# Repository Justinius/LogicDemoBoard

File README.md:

# LogicDemoBoard
PCB for simple logic demo

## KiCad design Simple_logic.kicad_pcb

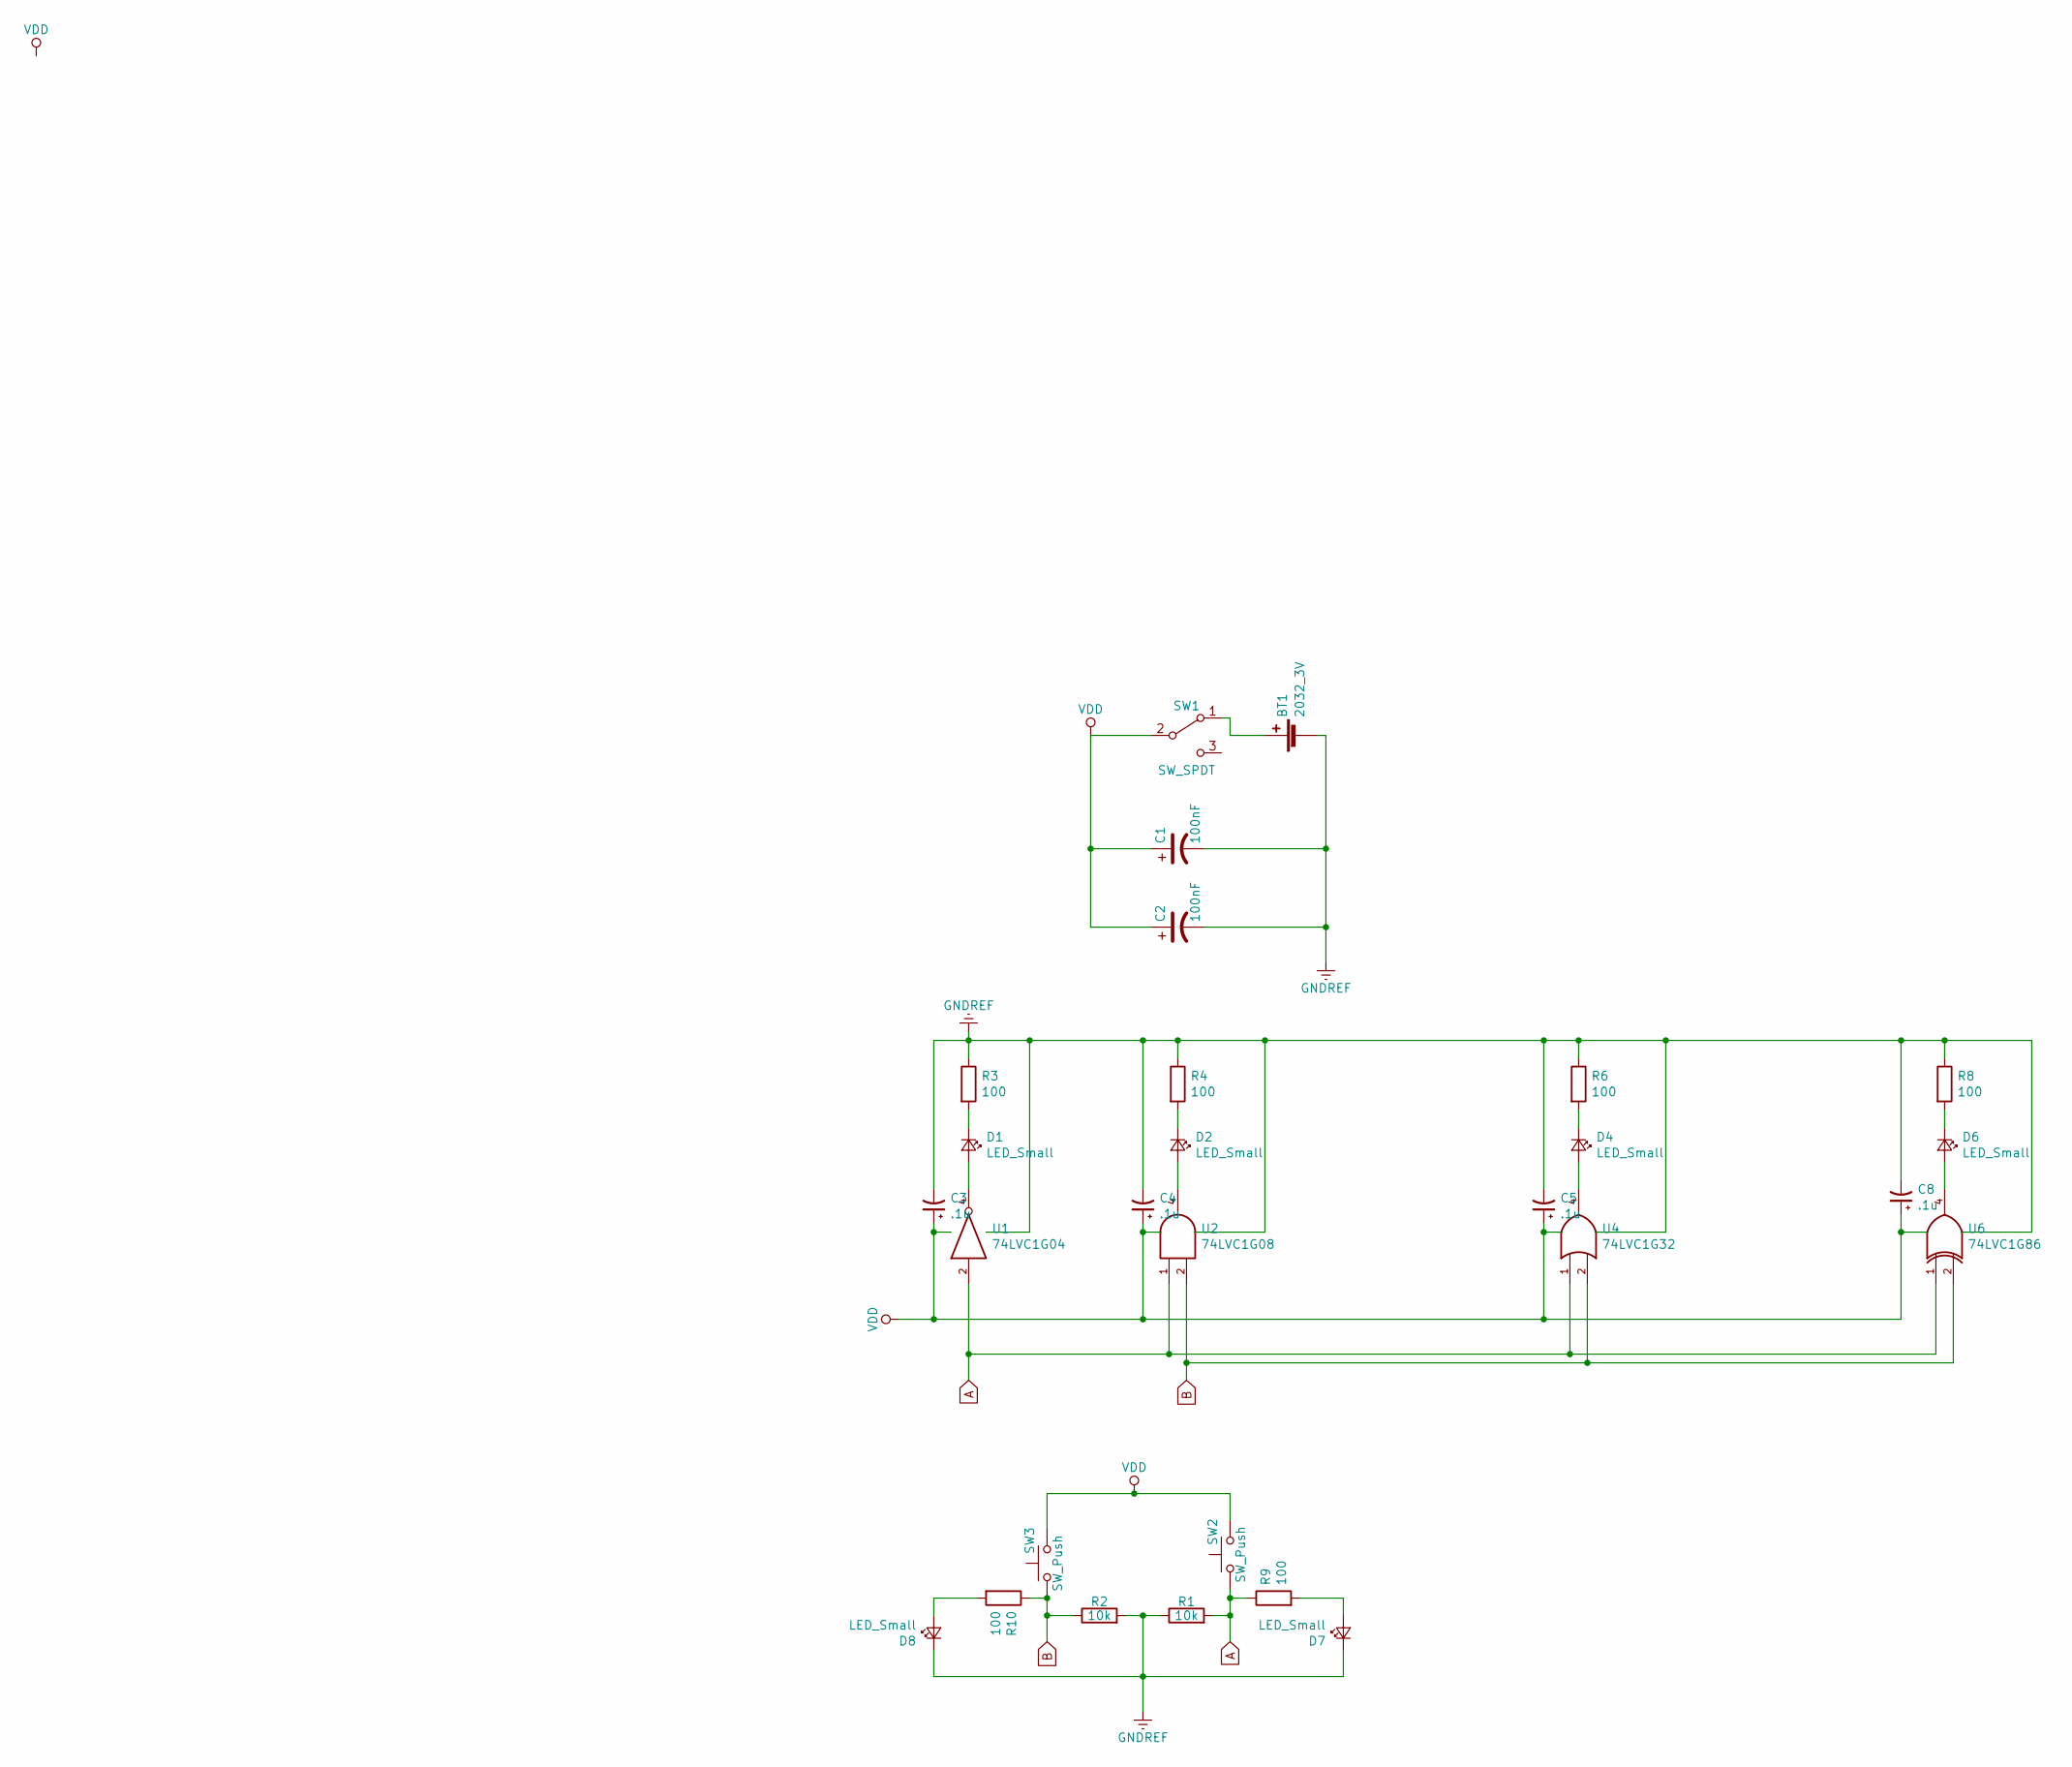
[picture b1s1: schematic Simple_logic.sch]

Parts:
BT1: 2032_3V; Keystone_3034_1x20mm-CoinCell
C1, C2: 100nF; C_0603_HandSoldering
C3, C4, C5, C8: .1u; C_0603_HandSoldering
D1, D2, D4, D6, D7, D8: LED_Small; LED_0805_HandSoldering
R1, R2: 10k; R_0603_HandSoldering
R3, R4, R6, R8, R9, R10: 100; R_0603_HandSoldering
SW1: SW_SPDT; SW_SPDT_CK-JS102011SAQN
SW2, SW3: SW_Push; SW_SPST_PTS645
U1: 74LVC1G04; SOT-23-5_HandSoldering
U2: 74LVC1G08; SOT-23-5_HandSoldering
U4: 74LVC1G32; SOT-23-5_HandSoldering
U6: 74LVC1G86; SOT-23-5_HandSoldering

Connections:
A: R1.2, R9.1, SW2.1, U1.2, U2.1, U4.1, U6.1
B: R2.1, R10.1, SW3.1, U2.2, U4.2, U6.2
GND: BT1.2 (-), C1.2, C2.2, C3.2, C4.2, C5.2, C8.2, D7.1 (K), D8.1 (K), R1.1, R2.2, R3.1, R4.1, R6.1, R8.1, U1.3 (GND), U2.3 (GND), U4.3 (GND), U6.3 (GND); also elsewhere on the board
unnamed: BT1.1 (+), SW1.1 (A)
unnamed: D1.1 (K), R3.2
unnamed: D1.2 (A), U1.4
unnamed: D2.1 (K), R4.2
unnamed: D2.2 (A), U2.4
unnamed: D4.1 (K), R6.2
unnamed: D4.2 (A), U4.4
unnamed: D6.1 (K), R8.2
unnamed: D6.2 (A), U6.4
unnamed: D7.2 (A), R9.2
unnamed: D8.2 (A), R10.2
VCC: C1.1, C2.1, C3.1, C4.1, C5.1, C8.1, SW1.2 (B), SW2.2, SW3.2, U1.5 (VCC), U2.5 (VCC), U4.5 (VCC), U6.5 (VCC); also elsewhere on the board

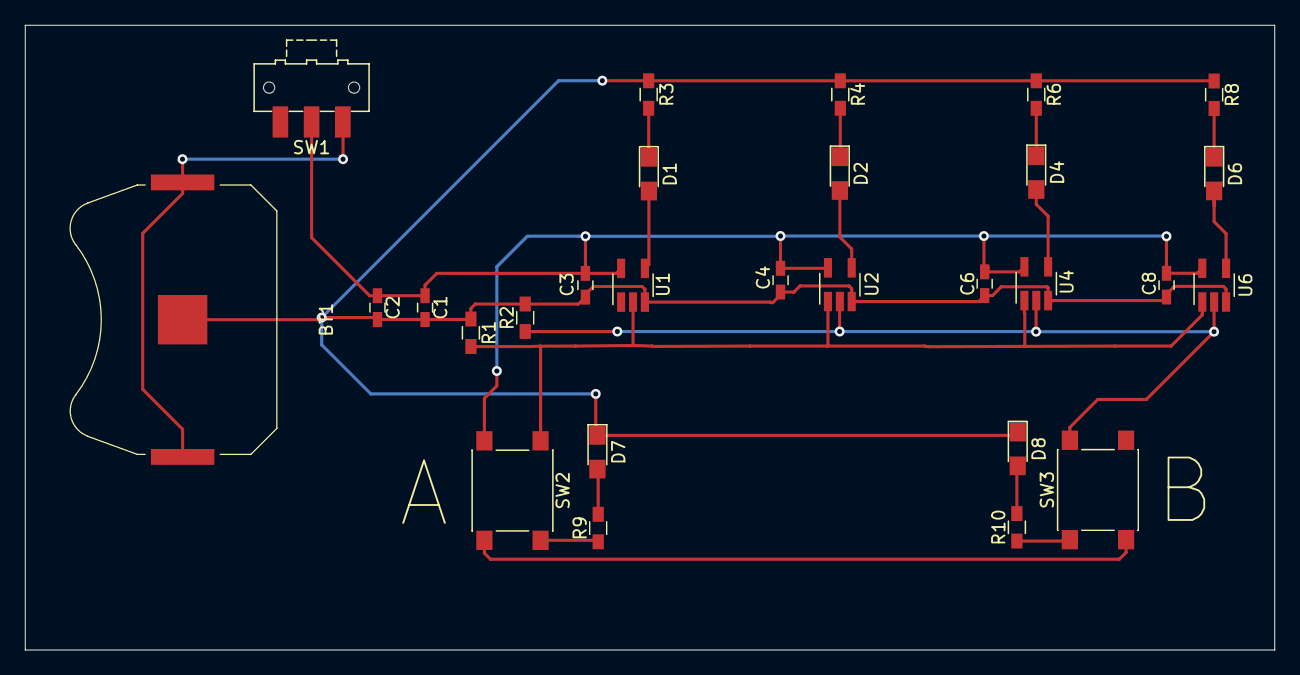
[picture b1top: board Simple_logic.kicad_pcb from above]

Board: 2 copper layers, 100.0 x 50.0 mm, 28 parts (0 on the bottom side), 15 nets.

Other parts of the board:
C6: .1u; C_0603_HandSoldering

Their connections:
GND: C6.2; also elsewhere on the board
VCC: C6.1; also elsewhere on the board
